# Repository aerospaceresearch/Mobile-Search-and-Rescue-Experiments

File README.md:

# thebeacon
the beacon a DGSN station shall track, everywhere, anytime

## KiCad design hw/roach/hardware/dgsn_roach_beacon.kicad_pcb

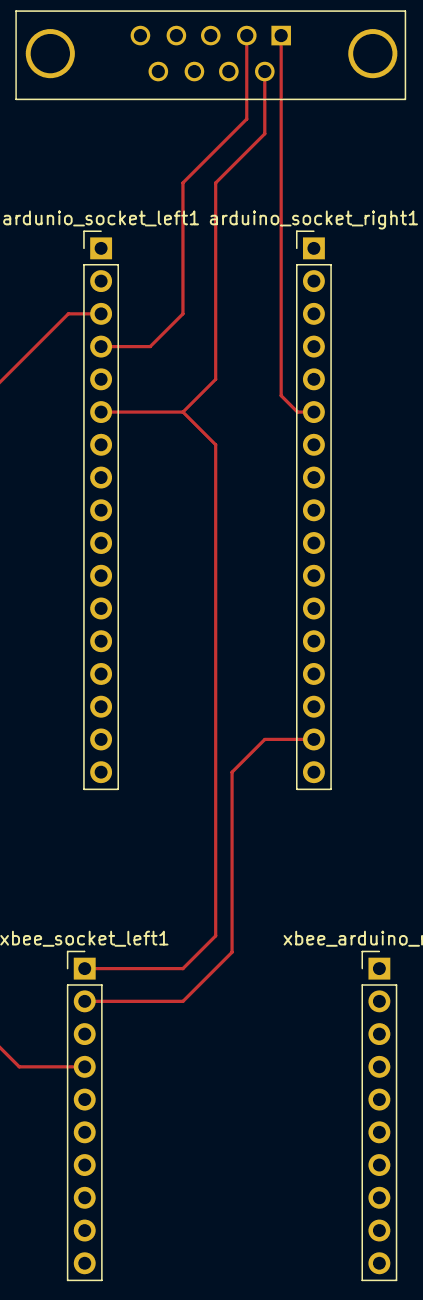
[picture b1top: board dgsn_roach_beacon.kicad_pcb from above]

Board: 2 copper layers, 5 parts (0 on the bottom side), 5 nets.

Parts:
J1: DB9_FEMALE_MountingHoles; DB9FD
arduino_socket_right1: CONN_01X17; Socket_Strip_Straight_1x17_Pitch2.54mm
ardunio_socket_left1: CONN_01X17; Socket_Strip_Straight_1x17_Pitch2.54mm
xbee_arduino_right1: CONN_01X10; Socket_Strip_Straight_1x10_Pitch2.54mm
xbee_socket_left1: CONN_01X10; Socket_Strip_Straight_1x10_Pitch2.54mm

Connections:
/3.3V: arduino_socket_right1.16, xbee_socket_left1.2
/TX_roach: J1.2, ardunio_socket_left1.4
/TX_to_xbee: ardunio_socket_left1.3, xbee_socket_left1.4
GND: J1.6, ardunio_socket_left1.6, xbee_socket_left1.1
VCC: J1.1, arduino_socket_right1.6

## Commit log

2017-05-20 initial commit of the beacon hw
    initial commit of the beacon hw
2017-08-21 copying roach hw layouts to hw-folder
2017-08-21 code and results of the longterm gps position precision test
    python code
    result htmls
    and graphs
2017-08-21 uploading the source files of the measurement #1
    data of the first sensor, #1
2017-08-21 uploading the source files of the measurement #2
    data of the second sensor, #2
